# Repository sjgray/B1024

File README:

B1024 Clone Project (C)2020 Steve J. Gray.
=================== Started May 2020

Intro
-----

This is a project to clone the
Anderson Engineering 1024K Board for CBM-II.
Mike Naberezny purchased a bare board from Bill Degnan and
then scanned it and posted pictures on his web page:

http://mikenaberezny.com/hardware/cbm-ii/b1024-ram-expansion-board/

Component Reference
-------------------

Since the board has no references for the IC's
I have numbered them based on the following:

- With the board oriented with pin 1's on the LEFT or TOP.
- U1 is at the top left.
- Connectors P7 and J6 are below it
- U2 is at the bottom left.
- U3 to U12 are to the right.

The DRAMs are:
- U12 to U19 on the top row
- U29 to U27
- U28 to U35
- U36 to U43 on the bottom row

Then U44 to U47 on the right of the board
P9 and J9 are between U46 and U47

IC PARTS
--------

U1 - 6264 /
U2 - ?

U3 - 74S74 /
U4 - 74S0?
U5 - 74S02 /
U6 - ?
U7 - 74S153 /
U8 - 74S153 /
U9 - 74S153 /
U10- 74S153 /
U11- 74S153 /

U12 to U43 - 41256 DRAM /

U44- 74S157
U45- 74S139 /
U46- 74S157 /
U47- 74S153

PARTS (From Mike N)
=====

* Sockets:
    - 28 pin x 1 for 6264
    - 16 pin x32 for DRAMs
    - 16 pin x11 for other chips
    - 14 pin x 3 for other chips
* Jumpers
* 41256 DRAMx32
* 6264 SRAM
* 74S02
* 74S08
* 74S74
* 74S85
* 74S139
* 74S153
* 74S157
* 74LS393
* Capacitor 0.1uF x 51
* Resistor 4.7K .25W
* Resistor Networks:
   - 22 ohm 4 section / 8 pin
   - 22 ohm 5 section / 8 pin
   - 4.7K   7 section / 8 pin
   - 4.7K   9 section / 10 pin
   - 10K    9 section / 10 pin

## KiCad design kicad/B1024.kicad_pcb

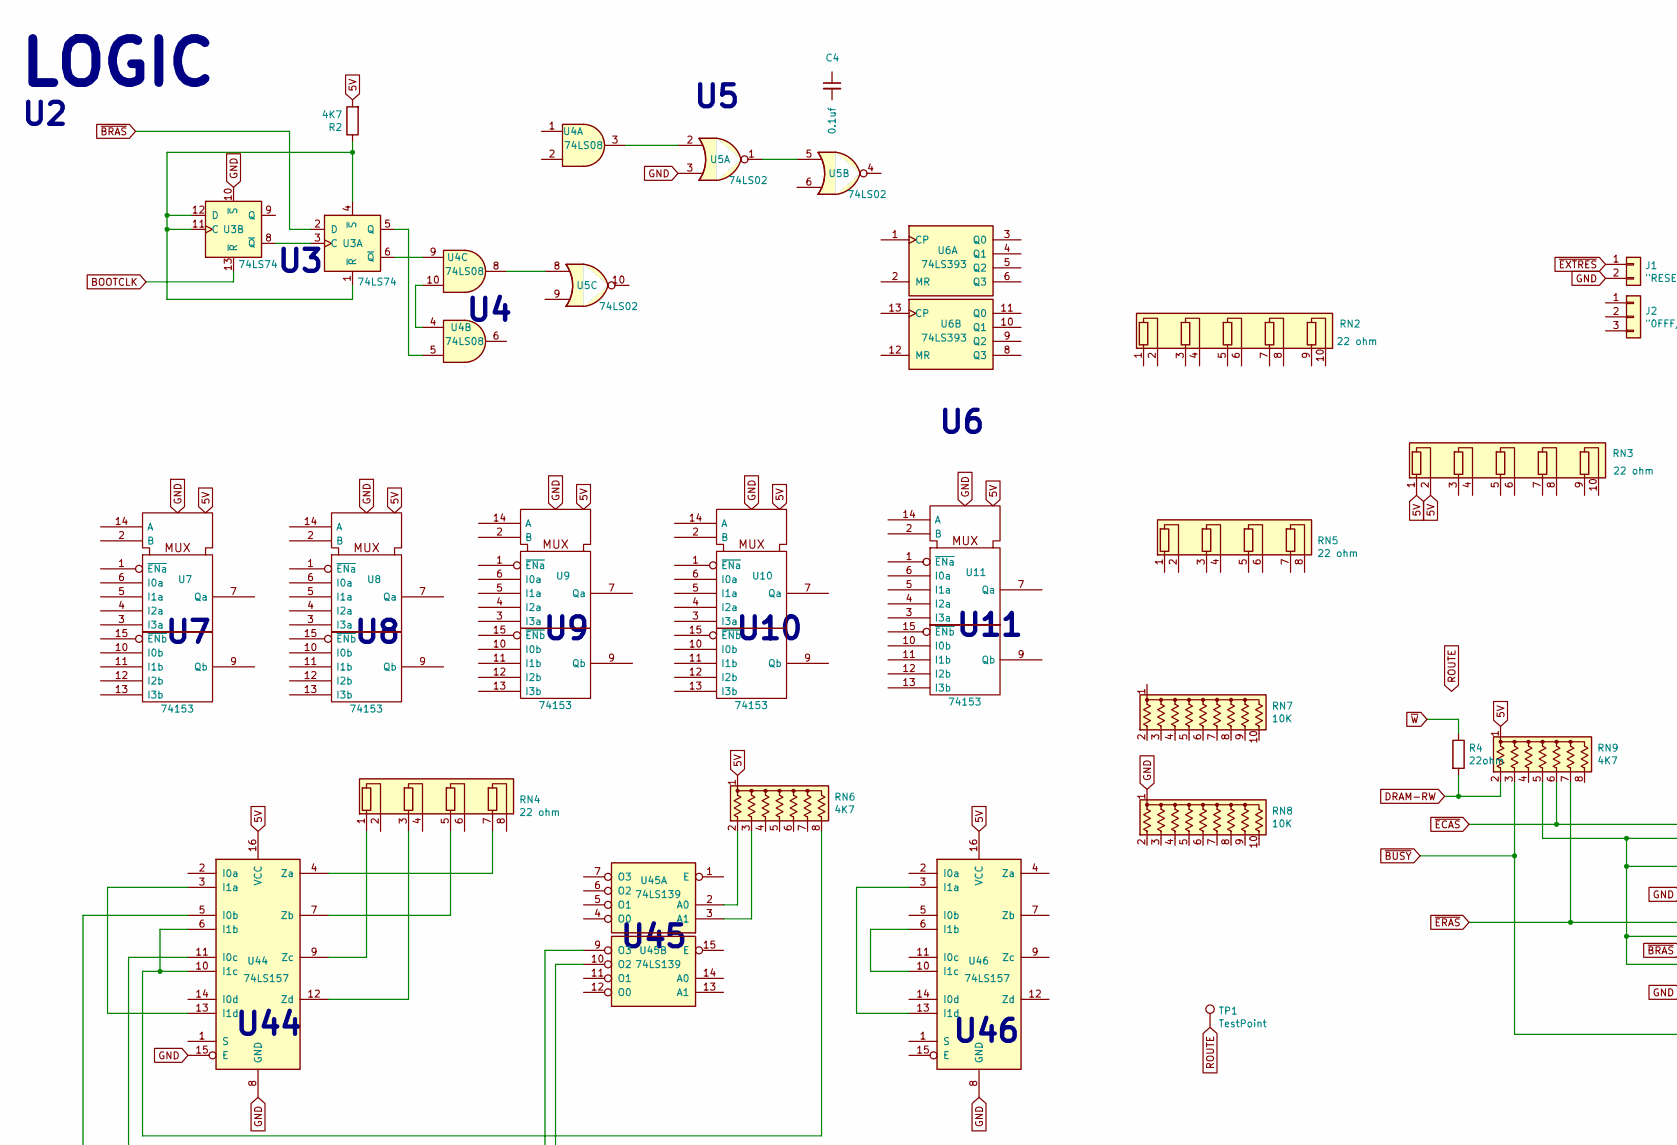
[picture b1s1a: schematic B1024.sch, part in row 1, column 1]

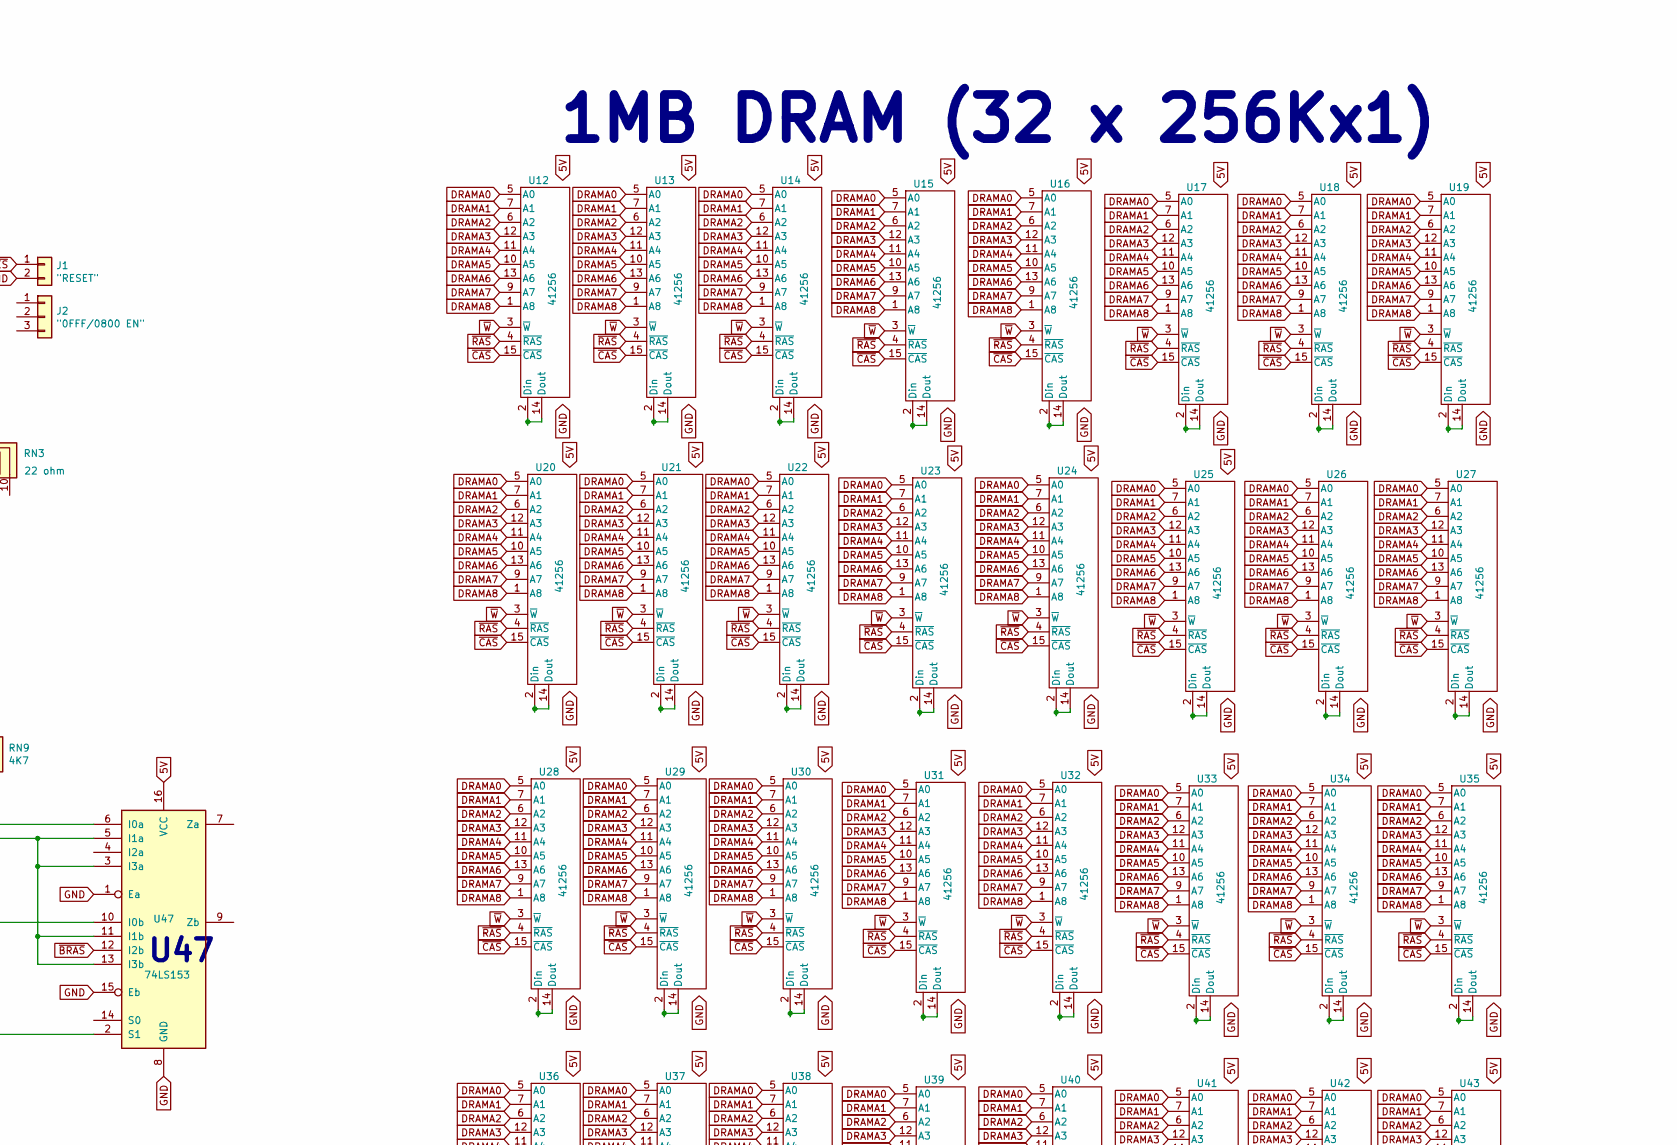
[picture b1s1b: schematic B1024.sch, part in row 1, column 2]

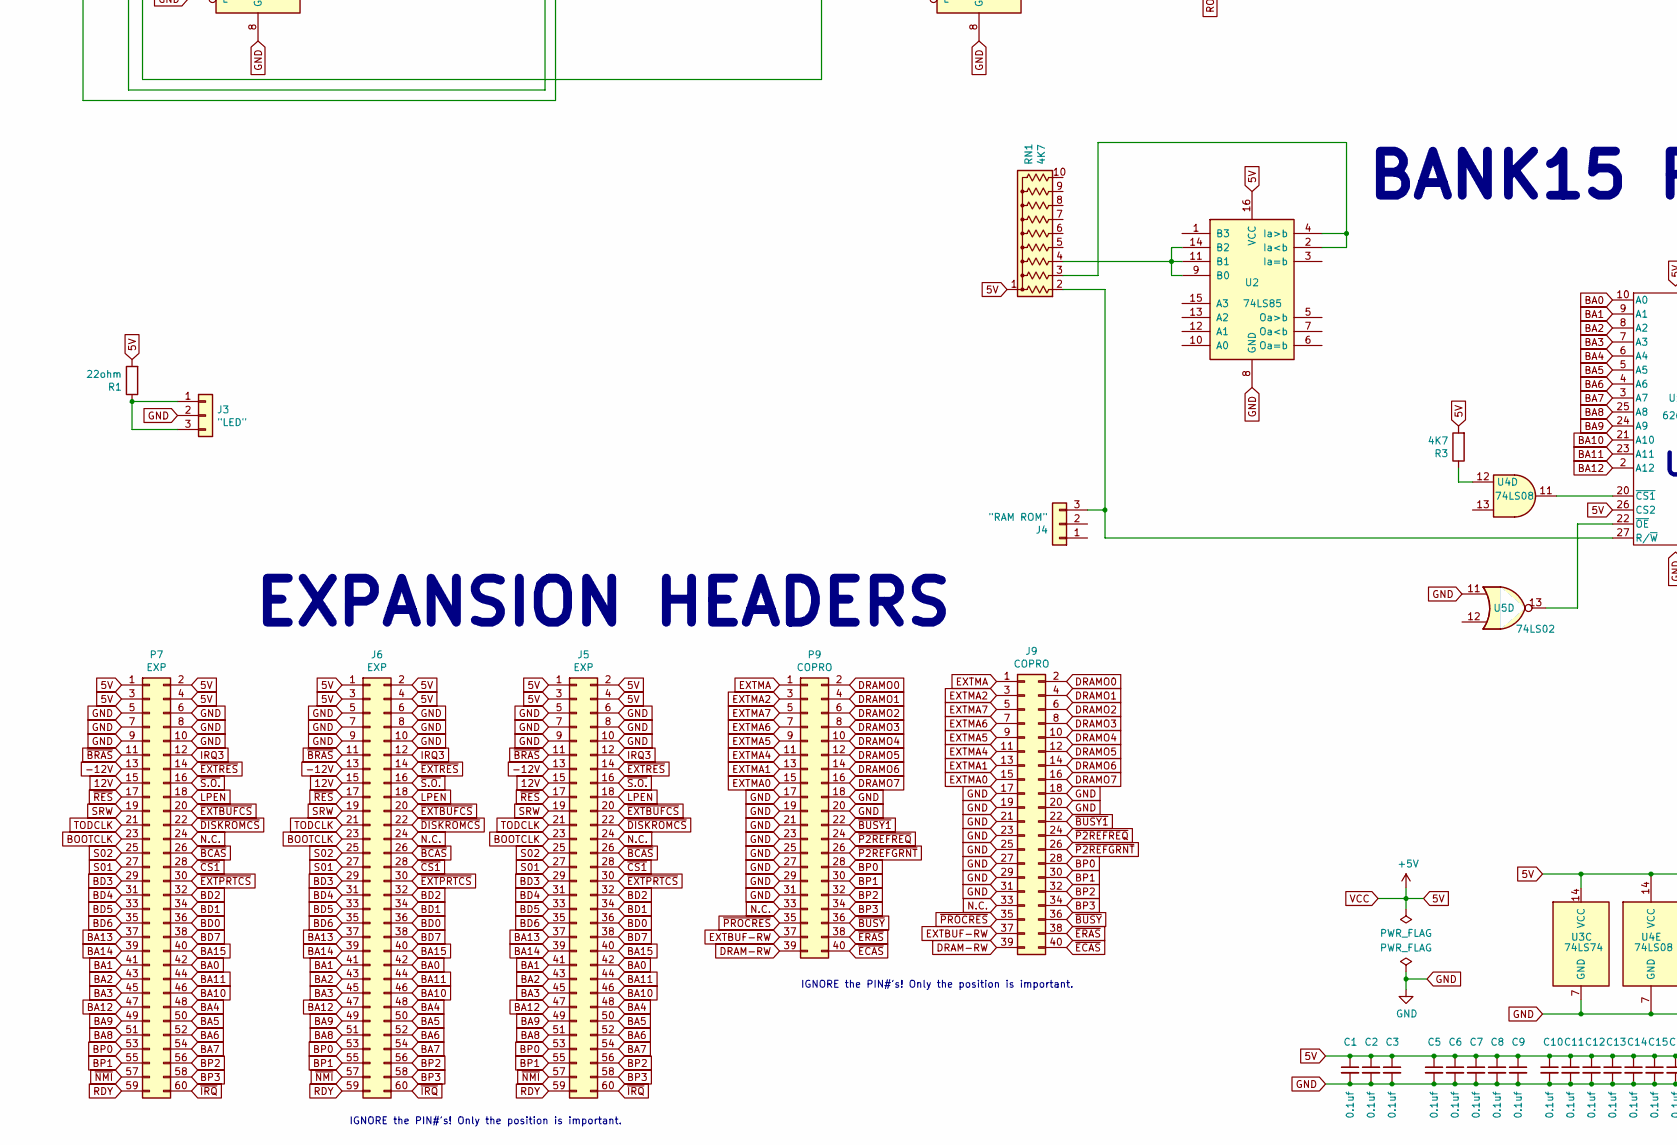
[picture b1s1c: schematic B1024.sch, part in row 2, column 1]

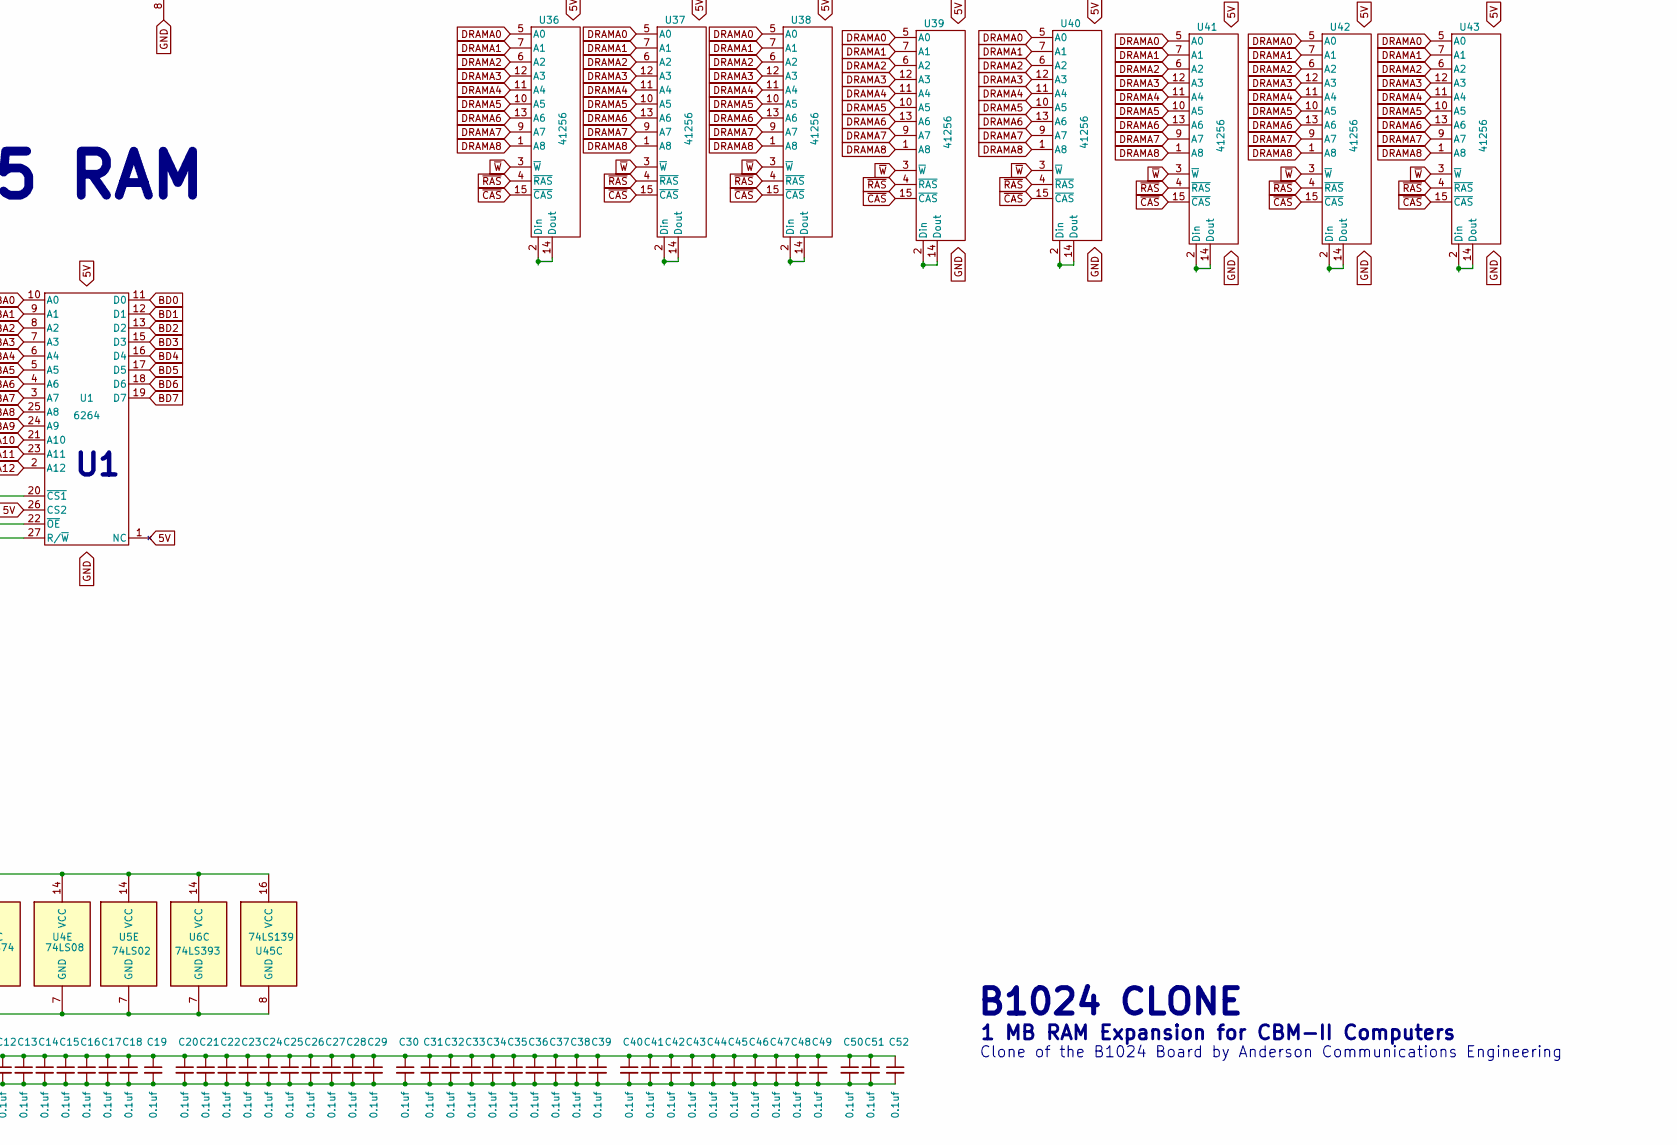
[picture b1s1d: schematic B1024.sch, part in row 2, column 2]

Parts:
C1, C2, C3, C4, C5, C6, C7, C8, C9, C10, C11, C12, C13, C14, C15, C16, C17, C18, C19, C20, C21, C22, C23, C24, C25, C26, C27, C28, C29, C30, C31, C32, C33, C34, C35, C36, C37, C38, C39, C40, C41, C42, C43, C44, C45, C46, C47, C48, C49, C50, C51, C52: 0.1uf; C_Disc_D4.7mm_W2.5mm_P5.00mm
J1: \"RESET\"; PinHeader_1x02_P2.54mm_Horizontal
J2: \"0FFF/0800 EN\"; PinHeader_1x03_P2.54mm_Horizontal
J3: \"LED\"; PinHeader_1x03_P2.54mm_Horizontal
J4: \"RAM ROM\"; PinHeader_1x03_P2.54mm_Horizontal
J5, J6: EXP; PinHeader_2x30_P2.54mm_Vertical
J9: COPRO; PinHeader_2x20_P2.54mm_Vertical
P7: EXP; PinHeader_2x30_P2.54mm_Vertical
P9: COPRO; PinHeader_2x20_P2.54mm_Vertical
R1, R4: 22ohm; R_Axial_DIN0207_L6.3mm_D2.5mm_P10.16mm_Horizontal
R2, R3: 4K7; R_Axial_DIN0207_L6.3mm_D2.5mm_P10.16mm_Horizontal
RN1: 4K7; R_Array_SIP10
RN2, RN3: 22 ohm; R_Array_SIP10
RN4, RN5: 22 ohm; R_Array_SIP8
RN6, RN9: 4K7; R_Array_SIP8
RN7, RN8: 10K; R_Array_SIP10
TP1: TestPoint; PinHeader_1x01_P2.54mm_Vertical
U1: 6264; DIP-28_W15.24mm
U2: 74LS85; DIP-16_W7.62mm
U3: 74LS74; DIP-14_W7.62mm
U4: 74LS08; DIP-14_W7.62mm
U5: 74LS02; DIP-14_W7.62mm
U6: 74LS393; DIP-14_W7.62mm
U7, U8, U9, U10, U11: 74153; DIP-16_W7.62mm
U12, U13, U14, U15, U16, U17, U18, U19, U20, U21, U22, U23, U24, U25, U26, U27, U28, U29, U30, U31, U32, U33, U34, U35, U36, U37, U38, U39, U40, U41, U42, U43: 41256; DIP-16_W7.62mm
U44, U46: 74LS157; DIP-16_W7.62mm
U45: 74LS139; DIP-16_W7.62mm
U47: 74LS153; DIP-16_W7.62mm

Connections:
5V: C1.1, C2.1, C3.1, C5.1, C6.1, C7.1, C8.1, C9.1, C10.1, C11.1, C12.1, C13.1, C14.1, C15.1, C16.1, C17.1, C18.1, C19.1, C20.1, C21.1, C22.1, C23.1, C24.1, C25.1, C26.1, C27.1, C28.1, C29.1, C30.1, C31.1, C32.1, C33.1, C34.1, C35.1, C36.1, C37.1, C38.1, C39.1, C40.1, C41.1, C42.1, C43.1, C44.1, C45.1, C46.1, C47.1, C48.1, C49.1, C50.1, C51.1, C52.1, J5.1, J5.2, J5.3, J5.4, J6.1, J6.2, J6.3, J6.4, P7.1, P7.2, P7.3, P7.4, R1.2, R2.2, R3.2, RN1.1 (common), RN3.1 (R1.1), RN3.2 (R1.2), RN6.1 (common), RN9.1 (common), U1.1 (NC), U1.26 (CS2), U1.28 (Vcc), U2.16 (VCC), U3.14 (VCC), U4.14 (VCC), U5.14 (VCC), U6.14 (VCC), U7.16 (VCC), U8.16 (VCC), U9.16 (VCC), U10.16 (VCC), U11.16 (VCC), U12.8 (Vcc), U13.8 (Vcc), U14.8 (Vcc), U15.8 (Vcc), U16.8 (Vcc), U17.8 (Vcc), U18.8 (Vcc), U19.8 (Vcc), U20.8 (Vcc), U21.8 (Vcc), U22.8 (Vcc), U23.8 (Vcc), U24.8 (Vcc), U25.8 (Vcc), U26.8 (Vcc), U27.8 (Vcc), U28.8 (Vcc), U29.8 (Vcc), U30.8 (Vcc), U31.8 (Vcc), U32.8 (Vcc), U33.8 (Vcc), U34.8 (Vcc), U35.8 (Vcc), U36.8 (Vcc), U37.8 (Vcc), U38.8 (Vcc), U39.8 (Vcc), U40.8 (Vcc), U41.8 (Vcc), U42.8 (Vcc), U43.8 (Vcc), U44.16 (VCC), U45.16 (VCC), U46.16 (VCC), U47.16 (VCC)
12V: J5.15, J6.15, P7.15
-12V: J5.13, J6.13, P7.13
BA0: J5.42, J6.42, P7.42, U1.10 (A0)
BA1: J5.41, J6.41, P7.41, U1.9 (A1)
BA2: J5.43, J6.43, P7.43, U1.8 (A2)
BA3: J5.45, J6.45, P7.45, U1.7 (A3)
BA4: J5.48, J6.48, P7.48, U1.6 (A4)
BA5: J5.50, J6.50, P7.50, U1.5 (A5)
BA6: J5.52, J6.52, P7.52, U1.4 (A6)
BA7: J5.54, J6.54, P7.54, U1.3 (A7)
BA8: J5.51, J6.51, P7.51, U1.25 (A8)
BA9: J5.49, J6.49, P7.49, U1.24 (A9)
BA10: J5.46, J6.46, P7.46, U1.21 (A10)
BA11: J5.44, J6.44, P7.44, U1.23 (A11)
BA12: J5.47, J6.47, P7.47, U1.2 (A12)
BA13: J5.37, J6.37, P7.37
BA14: J5.39, J6.39, P7.39
BA15: J5.40, J6.40, P7.40
BD0: J5.36, J6.36, P7.36, U1.11 (D0)
BD1: J5.34, J6.34, P7.34, U1.12 (D1)
BD2: J5.32, J6.32, P7.32, U1.13 (D2)
BD3: J5.29, J6.29, P7.29, U1.15 (D3)
BD4: J5.31, J6.31, P7.31, U1.16 (D4)
BD5: J5.33, J6.33, P7.33, U1.17 (D5)
BD6: J5.35, J6.35, P7.35, U1.18 (D6)
BD7: J5.38, J6.38, P7.38, U1.19 (D7)
BOOTCLK: J5.23, J6.23, P7.23, U3.13 (~R)
BP0: J5.53, J6.53, J9.28, P7.53, P9.28
BP1: J5.55, J6.55, J9.30, P7.55, P9.30
BP2: J5.56, J6.56, J9.32, P7.56, P9.32
BP3: J5.58, J6.58, J9.34, P7.58, P9.34
DRAM-RW: J9.39, P9.39, R4.2, RN9.2 (R1)
DRAMA0: U12.5 (A0), U13.5 (A0), U14.5 (A0), U15.5 (A0), U16.5 (A0), U17.5 (A0), U18.5 (A0), U19.5 (A0), U20.5 (A0), U21.5 (A0), U22.5 (A0), U23.5 (A0), U24.5 (A0), U25.5 (A0), U26.5 (A0), U27.5 (A0), U28.5 (A0), U29.5 (A0), U30.5 (A0), U31.5 (A0), U32.5 (A0), U33.5 (A0), U34.5 (A0), U35.5 (A0), U36.5 (A0), U37.5 (A0), U38.5 (A0), U39.5 (A0), U40.5 (A0), U41.5 (A0), U42.5 (A0), U43.5 (A0)
DRAMA1: U12.7 (A1), U13.7 (A1), U14.7 (A1), U15.7 (A1), U16.7 (A1), U17.7 (A1), U18.7 (A1), U19.7 (A1), U20.7 (A1), U21.7 (A1), U22.7 (A1), U23.7 (A1), U24.7 (A1), U25.7 (A1), U26.7 (A1), U27.7 (A1), U28.7 (A1), U29.7 (A1), U30.7 (A1), U31.7 (A1), U32.7 (A1), U33.7 (A1), U34.7 (A1), U35.7 (A1), U36.7 (A1), U37.7 (A1), U38.7 (A1), U39.7 (A1), U40.7 (A1), U41.7 (A1), U42.7 (A1), U43.7 (A1)
DRAMA2: U12.6 (A2), U13.6 (A2), U14.6 (A2), U15.6 (A2), U16.6 (A2), U17.6 (A2), U18.6 (A2), U19.6 (A2), U20.6 (A2), U21.6 (A2), U22.6 (A2), U23.6 (A2), U24.6 (A2), U25.6 (A2), U26.6 (A2), U27.6 (A2), U28.6 (A2), U29.6 (A2), U30.6 (A2), U31.6 (A2), U32.6 (A2), U33.6 (A2), U34.6 (A2), U35.6 (A2), U36.6 (A2), U37.6 (A2), U38.6 (A2), U39.6 (A2), U40.6 (A2), U41.6 (A2), U42.6 (A2), U43.6 (A2)
DRAMA3: U12.12 (A3), U13.12 (A3), U14.12 (A3), U15.12 (A3), U16.12 (A3), U17.12 (A3), U18.12 (A3), U19.12 (A3), U20.12 (A3), U21.12 (A3), U22.12 (A3), U23.12 (A3), U24.12 (A3), U25.12 (A3), U26.12 (A3), U27.12 (A3), U28.12 (A3), U29.12 (A3), U30.12 (A3), U31.12 (A3), U32.12 (A3), U33.12 (A3), U34.12 (A3), U35.12 (A3), U36.12 (A3), U37.12 (A3), U38.12 (A3), U39.12 (A3), U40.12 (A3), U41.12 (A3), U42.12 (A3), U43.12 (A3)
DRAMA4: U12.11 (A4), U13.11 (A4), U14.11 (A4), U15.11 (A4), U16.11 (A4), U17.11 (A4), U18.11 (A4), U19.11 (A4), U20.11 (A4), U21.11 (A4), U22.11 (A4), U23.11 (A4), U24.11 (A4), U25.11 (A4), U26.11 (A4), U27.11 (A4), U28.11 (A4), U29.11 (A4), U30.11 (A4), U31.11 (A4), U32.11 (A4), U33.11 (A4), U34.11 (A4), U35.11 (A4), U36.11 (A4), U37.11 (A4), U38.11 (A4), U39.11 (A4), U40.11 (A4), U41.11 (A4), U42.11 (A4), U43.11 (A4)
DRAMA5: U12.10 (A5), U13.10 (A5), U14.10 (A5), U15.10 (A5), U16.10 (A5), U17.10 (A5), U18.10 (A5), U19.10 (A5), U20.10 (A5), U21.10 (A5), U22.10 (A5), U23.10 (A5), U24.10 (A5), U25.10 (A5), U26.10 (A5), U27.10 (A5), U28.10 (A5), U29.10 (A5), U30.10 (A5), U31.10 (A5), U32.10 (A5), U33.10 (A5), U34.10 (A5), U35.10 (A5), U36.10 (A5), U37.10 (A5), U38.10 (A5), U39.10 (A5), U40.10 (A5), U41.10 (A5), U42.10 (A5), U43.10 (A5)
DRAMA6: U12.13 (A6), U13.13 (A6), U14.13 (A6), U15.13 (A6), U16.13 (A6), U17.13 (A6), U18.13 (A6), U19.13 (A6), U20.13 (A6), U21.13 (A6), U22.13 (A6), U23.13 (A6), U24.13 (A6), U25.13 (A6), U26.13 (A6), U27.13 (A6), U28.13 (A6), U29.13 (A6), U30.13 (A6), U31.13 (A6), U32.13 (A6), U33.13 (A6), U34.13 (A6), U35.13 (A6), U36.13 (A6), U37.13 (A6), U38.13 (A6), U39.13 (A6), U40.13 (A6), U41.13 (A6), U42.13 (A6), U43.13 (A6)
DRAMA7: U12.9 (A7), U13.9 (A7), U14.9 (A7), U15.9 (A7), U16.9 (A7), U17.9 (A7), U18.9 (A7), U19.9 (A7), U20.9 (A7), U21.9 (A7), U22.9 (A7), U23.9 (A7), U24.9 (A7), U25.9 (A7), U26.9 (A7), U27.9 (A7), U28.9 (A7), U29.9 (A7), U30.9 (A7), U31.9 (A7), U32.9 (A7), U33.9 (A7), U34.9 (A7), U35.9 (A7), U36.9 (A7), U37.9 (A7), U38.9 (A7), U39.9 (A7), U40.9 (A7), U41.9 (A7), U42.9 (A7), U43.9 (A7)
DRAMA8: U12.1 (A8), U13.1 (A8), U14.1 (A8), U15.1 (A8), U16.1 (A8), U17.1 (A8), U18.1 (A8), U19.1 (A8), U20.1 (A8), U21.1 (A8), U22.1 (A8), U23.1 (A8), U24.1 (A8), U25.1 (A8), U26.1 (A8), U27.1 (A8), U28.1 (A8), U29.1 (A8), U30.1 (A8), U31.1 (A8), U32.1 (A8), U33.1 (A8), U34.1 (A8), U35.1 (A8), U36.1 (A8), U37.1 (A8), U38.1 (A8), U39.1 (A8), U40.1 (A8), U41.1 (A8), U42.1 (A8), U43.1 (A8)
DRAMO0: J9.2, P9.2
DRAMO1: J9.4, P9.4
DRAMO2: J9.6, P9.6
DRAMO3: J9.8, P9.8
DRAMO4: J9.10, P9.10
DRAMO5: J9.12, P9.12
DRAMO6: J9.14, P9.14
DRAMO7: J9.16, P9.16
EXTBUF-RW: J9.37, P9.37
EXTMA: J9.1, P9.1
EXTMA0: J9.15, P9.15
EXTMA1: J9.13, P9.13
EXTMA2: J9.3, P9.3
EXTMA4: J9.11, P9.11
EXTMA5: J9.9, P9.9
EXTMA6: J9.7, P9.7
EXTMA7: J9.5, P9.5
GND: C1.2, C2.2, C3.2, C5.2, C6.2, C7.2, C8.2, C9.2, C10.2, C11.2, C12.2, C13.2, C14.2, C15.2, C16.2, C17.2, C18.2, C19.2, C20.2, C21.2, C22.2, C23.2, C24.2, C25.2, C26.2, C27.2, C28.2, C29.2, C30.2, C31.2, C32.2, C33.2, C34.2, C35.2, C36.2, C37.2, C38.2, C39.2, C40.2, C41.2, C42.2, C43.2, C44.2, C45.2, C46.2, C47.2, C48.2, C49.2, C50.2, C51.2, C52.2, J1.2, J3.2, J5.5, J5.6, J5.7, J5.8, J5.9, J5.10, J6.5, J6.6, J6.7, J6.8, J6.9, J6.10, J9.17, J9.18, J9.19, J9.20, J9.21, J9.23, J9.25, J9.27, J9.29, J9.31, P7.5, P7.6, P7.7, P7.8, P7.9, P7.10, P9.17, P9.18, P9.19, P9.20, P9.21, P9.23, P9.25, P9.27, P9.29, P9.31, RN8.1 (common), U1.14 (GND), U2.8 (GND), U3.7 (GND), U3.10 (~S), U4.7 (GND), U5.3, U5.7 (GND), U5.11, U6.7 (GND), U7.8 (GND), U8.8 (GND), U9.8 (GND), U10.8 (GND), U11.8 (GND), U12.16 (GND), U13.16 (GND), U14.16 (GND), U15.16 (GND), U16.16 (GND), U17.16 (GND), U18.16 (GND), U19.16 (GND), U20.16 (GND), U21.16 (GND), U22.16 (GND), U23.16 (GND), U24.16 (GND), U25.16 (GND), U26.16 (GND), U27.16 (GND), U28.16 (GND), U29.16 (GND), U30.16 (GND), U31.16 (GND), U32.16 (GND), U33.16 (GND), U34.16 (GND), U35.16 (GND), U36.16 (GND), U37.16 (GND), U38.16 (GND), U39.16 (GND), U40.16 (GND), U41.16 (GND), U42.16 (GND), U43.16 (GND), U44.8 (GND), U44.15 (E), U45.8 (GND), U46.8 (GND), U47.1 (Ea), U47.8 (GND), U47.15 (Eb)
IRQ3: J5.12, J6.12, P7.12
LPEN: J5.18, J6.18, P7.18
N.C.: J5.24, J6.24, J9.33, P7.24, P9.33
unnamed: J3.1, J3.3, R1.1
unnamed: J4.3, RN1.2 (R1), U1.27 (R/~W)
unnamed: R2.1, U3.1 (~R), U3.4 (~S), U3.11 (C), U3.12 (D)
unnamed: R3.1, U4.12
unnamed: RN1.3 (R2), U2.2 (Ia<b), U2.4 (Ia>b)
unnamed: RN1.4 (R3), U2.9 (B0), U2.11 (B1), U2.14 (B2)
unnamed: RN4.1 (R1.1), U44.9 (Zc)
unnamed: RN4.3 (R2.1), U44.12 (Zd)
unnamed: RN4.5 (R3.1), U44.7 (Zb)
unnamed: RN4.7 (R4.1), U44.4 (Za)
unnamed: RN6.2 (R1), U45.2 (A0)
unnamed: RN6.3 (R2), U45.3 (A1)
unnamed: RN6.8 (R7), U44.6 (I1b), U44.10 (I1c)
unnamed: RN9.5 (R4), U47.3 (I3a), U47.5 (I1a), U47.11 (I1b), U47.13 (I3b)
unnamed: U1.20 (~CS1), U4.11
unnamed: U1.22 (~OE), U5.13
unnamed: U3.3 (C), U3.8 (~Q)
unnamed: U3.5 (Q), U4.5
unnamed: U3.6 (~Q), U4.9
unnamed: U4.3, U5.2
unnamed: U4.8, U5.8
unnamed: U4.4, U4.10
unnamed: U5.1, U5.5
unnamed: U12.2 (Din), U12.14 (Dout)
unnamed: U13.2 (Din), U13.14 (Dout)
unnamed: U14.2 (Din), U14.14 (Dout)
unnamed: U15.2 (Din), U15.14 (Dout)
unnamed: U16.2 (Din), U16.14 (Dout)
unnamed: U17.2 (Din), U17.14 (Dout)
unnamed: U18.2 (Din), U18.14 (Dout)
unnamed: U19.2 (Din), U19.14 (Dout)
unnamed: U20.2 (Din), U20.14 (Dout)
unnamed: U21.2 (Din), U21.14 (Dout)
unnamed: U22.2 (Din), U22.14 (Dout)
unnamed: U23.2 (Din), U23.14 (Dout)
unnamed: U24.2 (Din), U24.14 (Dout)
unnamed: U25.2 (Din), U25.14 (Dout)
unnamed: U26.2 (Din), U26.14 (Dout)
unnamed: U27.2 (Din), U27.14 (Dout)
unnamed: U28.2 (Din), U28.14 (Dout)
unnamed: U29.2 (Din), U29.14 (Dout)
unnamed: U30.2 (Din), U30.14 (Dout)
unnamed: U31.2 (Din), U31.14 (Dout)
unnamed: U32.2 (Din), U32.14 (Dout)
unnamed: U33.2 (Din), U33.14 (Dout)
unnamed: U34.2 (Din), U34.14 (Dout)
unnamed: U35.2 (Din), U35.14 (Dout)
unnamed: U36.2 (Din), U36.14 (Dout)
unnamed: U37.2 (Din), U37.14 (Dout)
unnamed: U38.2 (Din), U38.14 (Dout)
unnamed: U39.2 (Din), U39.14 (Dout)
unnamed: U40.2 (Din), U40.14 (Dout)
unnamed: U41.2 (Din), U41.14 (Dout)
unnamed: U42.2 (Din), U42.14 (Dout)
unnamed: U43.2 (Din), U43.14 (Dout)
unnamed: U44.5 (I0b), U45.10 (O2)
unnamed: U44.11 (I0c), U45.9 (O3)
unnamed: U44.3 (I1a), U44.13 (I1d)
unnamed: U46.6 (I1b), U46.10 (I1c)
unnamed: U46.3 (I1a), U46.13 (I1d)
RDY: J5.59, J6.59, P7.59
S01: J5.27, J6.27, P7.27
S02: J5.25, J6.25, P7.25
SRW: J5.19, J6.19, P7.19
TODCLK: J5.21, J6.21, P7.21
~BCAS: J5.26, J6.26, P7.26
~BRAS: J5.11, J6.11, P7.11, U3.2 (D), U47.12 (I2b)
~BUSY: J9.36, P9.36, RN9.3 (R2), U47.2 (S1)
~BUSY1: J9.22, P9.22
~CAS: U12.15 (~CAS), U13.15 (~CAS), U14.15 (~CAS), U15.15 (~CAS), U16.15 (~CAS), U17.15 (~CAS), U18.15 (~CAS), U19.15 (~CAS), U20.15 (~CAS), U21.15 (~CAS), U22.15 (~CAS), U23.15 (~CAS), U24.15 (~CAS), U25.15 (~CAS), U26.15 (~CAS), U27.15 (~CAS), U28.15 (~CAS), U29.15 (~CAS), U30.15 (~CAS), U31.15 (~CAS), U32.15 (~CAS), U33.15 (~CAS), U34.15 (~CAS), U35.15 (~CAS), U36.15 (~CAS), U37.15 (~CAS), U38.15 (~CAS), U39.15 (~CAS), U40.15 (~CAS), U41.15 (~CAS), U42.15 (~CAS), U43.15 (~CAS)
~CS1: J5.28, J6.28, P7.28
~DISKROMCS: J5.22, J6.22, P7.22
~ECAS: J9.40, P9.40, RN9.6 (R5), U47.6 (I0a)
~ERAS: J9.38, P9.38, RN9.7 (R6), U47.10 (I0b)
~EXTBUFCS: J5.20, J6.20, P7.20
~EXTPRTCS: J5.30, J6.30, P7.30
~EXTRES: J1.1, J5.14, J6.14, P7.14
~IRQ: J5.60, J6.60, P7.60
~NMI: J5.57, J6.57, P7.57
~P2REFGRNT: J9.26, P9.26
~P2REFREQ: J9.24, P9.24
~PROCRES: J9.35, P9.35
~RAS: U12.4 (~RAS), U13.4 (~RAS), U14.4 (~RAS), U15.4 (~RAS), U16.4 (~RAS), U17.4 (~RAS), U18.4 (~RAS), U19.4 (~RAS), U20.4 (~RAS), U21.4 (~RAS), U22.4 (~RAS), U23.4 (~RAS), U24.4 (~RAS), U25.4 (~RAS), U26.4 (~RAS), U27.4 (~RAS), U28.4 (~RAS), U29.4 (~RAS), U30.4 (~RAS), U31.4 (~RAS), U32.4 (~RAS), U33.4 (~RAS), U34.4 (~RAS), U35.4 (~RAS), U36.4 (~RAS), U37.4 (~RAS), U38.4 (~RAS), U39.4 (~RAS), U40.4 (~RAS), U41.4 (~RAS), U42.4 (~RAS), U43.4 (~RAS)
~RES: J5.17, J6.17, P7.17
~S.O.: J5.16, J6.16, P7.16
~W: R4.1, U12.3 (~W), U13.3 (~W), U14.3 (~W), U15.3 (~W), U16.3 (~W), U17.3 (~W), U18.3 (~W), U19.3 (~W), U20.3 (~W), U21.3 (~W), U22.3 (~W), U23.3 (~W), U24.3 (~W), U25.3 (~W), U26.3 (~W), U27.3 (~W), U28.3 (~W), U29.3 (~W), U30.3 (~W), U31.3 (~W), U32.3 (~W), U33.3 (~W), U34.3 (~W), U35.3 (~W), U36.3 (~W), U37.3 (~W), U38.3 (~W), U39.3 (~W), U40.3 (~W), U41.3 (~W), U42.3 (~W), U43.3 (~W)

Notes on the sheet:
1MB DRAM (32 x 256Kx1)
B1024 CLONE
EXPANSION HEADERS
BANK15 RAM
1 MB RAM Expansion for CBM-II Computers
Clone of the B1024 Board by Anderson Communications Engineering
LOGIC
U44
U45
U46
U47
U10
U11
IGNORE the PIN#'s! Only the position is important.

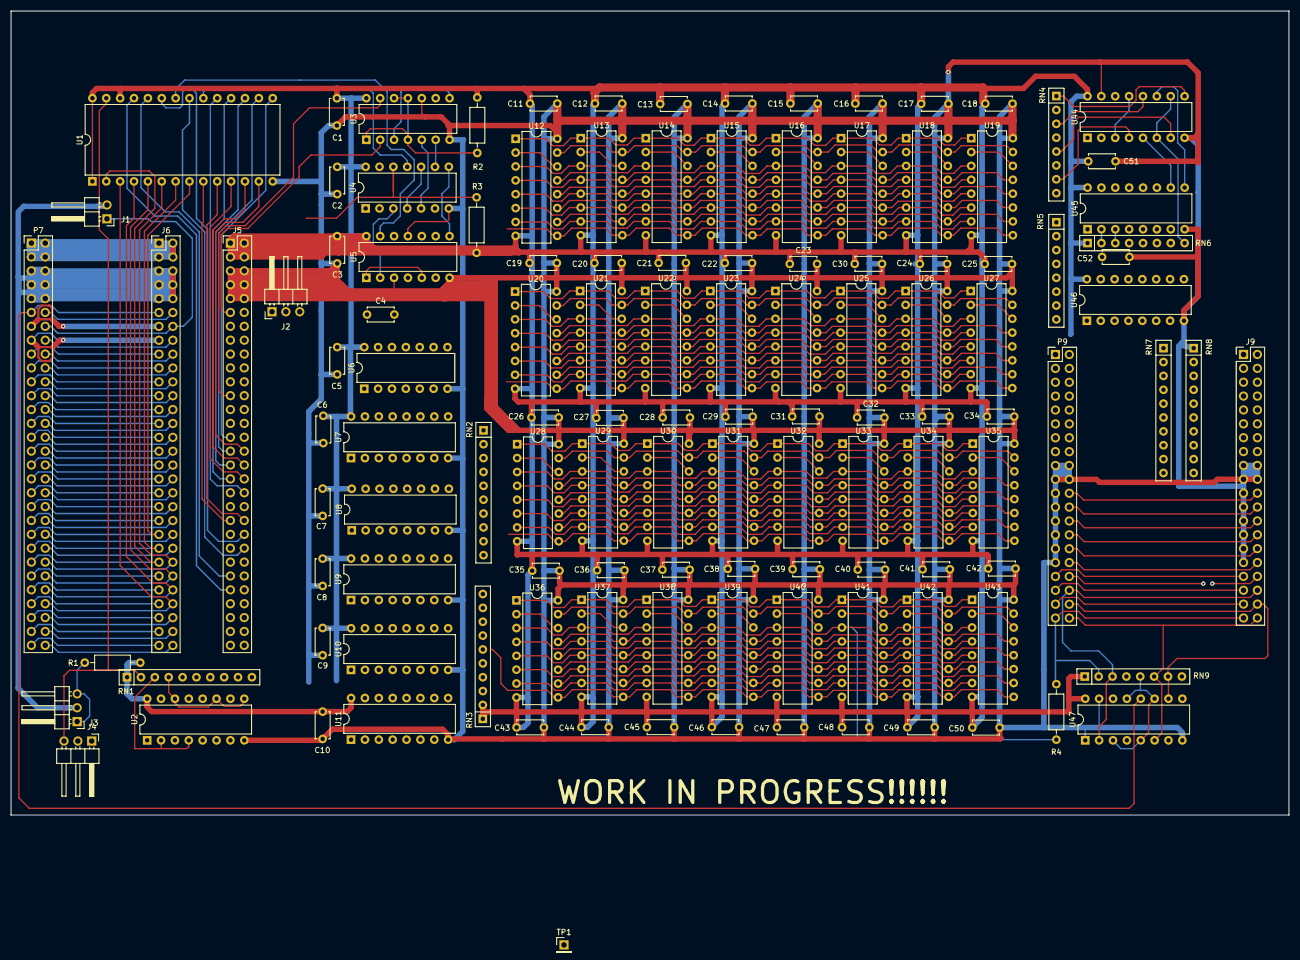
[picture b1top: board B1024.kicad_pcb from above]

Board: 2 copper layers, 234.0 x 147.2 mm, 122 parts (0 on the bottom side), 149 nets.

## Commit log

2020-05-15 :boom::camel: Added .gitattributes & .gitignore files
2020-05-15 Initial upload
    Includes pics, bom, and kicad files. Work in progress!
2020-05-15 Fix missing components
2020-05-15 Remove duplicate readme file
2020-05-16 Add remaining parts, prelim board layout
    Rotated pictures to match board layout. Added missing ics, resistors,
    and jumpers. Preliminary layout. Updated readme.
2020-05-16 Fix readme text. Add current progress pics
    Fix spelling mistakes in readme. Add schematic, board layout and board
    render pictures of current progress.
2020-05-25 Updated board layout with measurements
    Add measurement for port spacing
2020-06-07 Routing and circuit updates
    Schematic is starting to take shape. Route most common dram line and
    many expansion lines.
2020-06-07 Updated progress pics
    pcb and schematic pics
2023-08-02 Update README
    Add project status info
